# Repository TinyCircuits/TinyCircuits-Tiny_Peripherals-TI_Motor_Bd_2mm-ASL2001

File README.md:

# TinyCircuits Tiny Peripherals TI Motor Board 2mm
# ASL2001 Rev3

The design files are located under design_files/ for the TinyCircuits ASL2001 Rev 3 PCB.  This is a Tiny Peripheral TI Motor Board using the TI DRV8837, along with pads to solder to for all the signals.

Format is in Cadsoft Eagle format - Eagle version 6.2 was used for the original design.

For more infomation on this, check out the product page at TinyCircuits.com: https://tinycircuits.com/collections/tinylily/products/tinylily-motor-board

# License:

Design by TinyCircuits.
All design files are released under the Creative Commons Attribution Share-Alike 3.0 License, see the following link for details: http://creativecommons.org/licenses/by-sa/3.0

All text above must be included in any redistribution or derived design

This project uses designs and concepts developed as part of the Arduino project and the LilyPad project.  The TinyCircuits design files themselves (schematics, PCB and libraries) are not directly derived from these works' design files and have been created new, however the concepts and basic architecture behind the TinyDuino and TinyLily products are derived and we thank the hard work of the organizations below for their contributions to open-source hardware:
  
Original Arduino Uno Design by Team Arduino

LilyPad Arduino Design by Leah Buechley and Sparkfun Electronics

Please support the open-source hardware community

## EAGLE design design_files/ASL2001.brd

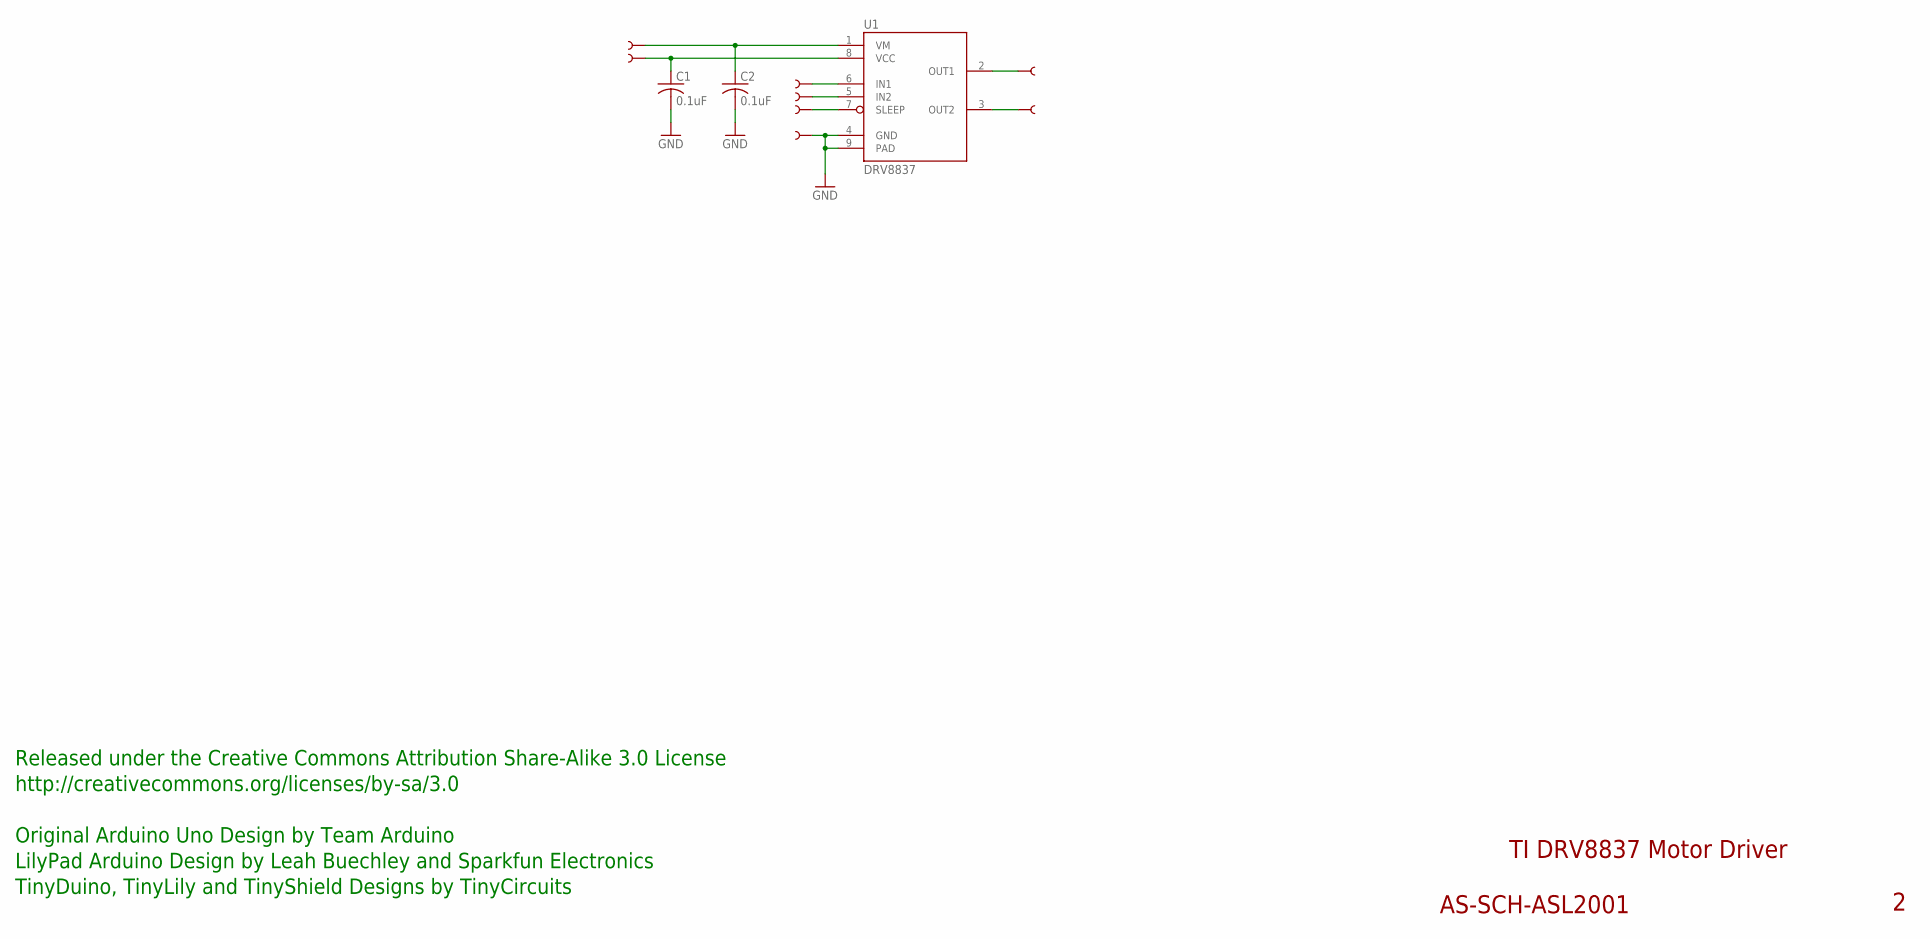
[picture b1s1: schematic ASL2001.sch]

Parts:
C1, C2: 0.1uF; C0402
U1: DRV8837; WSON-8
U$2, U$3, U$4, U$5, U$8, U$9, U$10, U$11: SEWTABTH_0402; SEWTAP_TH_0402

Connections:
GND: C1.2, C2.2, U1.4 (GND), U1.9 (PAD), U$9.1
unnamed: C1.1, U1.8 (VCC), U$2.1
unnamed: U1.7 (SLEEP), U$8.1
unnamed: U1.5 (IN2), U$5.1
unnamed: U1.6 (IN1), U$4.1
unnamed: C2.1, U1.1 (VM), U$3.1
unnamed: U1.2 (OUT1), U$10.1
unnamed: U1.3 (OUT2), U$11.1

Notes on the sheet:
TI DRV8837 Motor Driver
AS-SCH-ASL2001
Released under the Creative Commons Attribution Share-Alike 3.0 License
http://creativecommons.org/licenses/by-sa/3.0
LilyPad Arduino Design by Leah Buechley and Sparkfun Electronics
TinyDuino, TinyLily and TinyShield Designs by TinyCircuits
Original Arduino Uno Design by Team Arduino

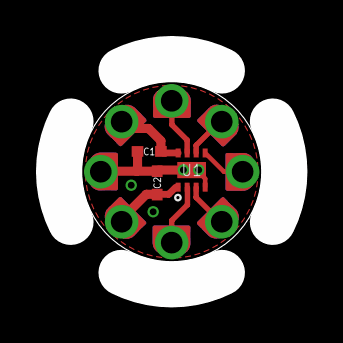
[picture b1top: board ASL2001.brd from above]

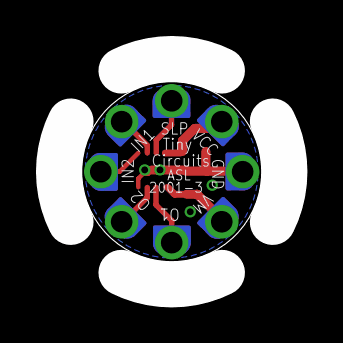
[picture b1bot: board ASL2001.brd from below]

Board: 2 copper layers, 10.0 x 10.0 mm, 12 parts (8 on the bottom side), 8 nets.

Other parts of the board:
U$6: DOCFIELD-TINYCIRCUITS-PCB

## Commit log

2012-09-16 Fixed Incorrect Name and document number
2013-06-30 Updated project link
2014-08-24 Updated Link
2019-01-04 update format
2019-05-30 TL Motor"
2019-05-31 pics
2019-05-31 croppy crop
2020-02-13 image
2020-08-28 Add CAD data
